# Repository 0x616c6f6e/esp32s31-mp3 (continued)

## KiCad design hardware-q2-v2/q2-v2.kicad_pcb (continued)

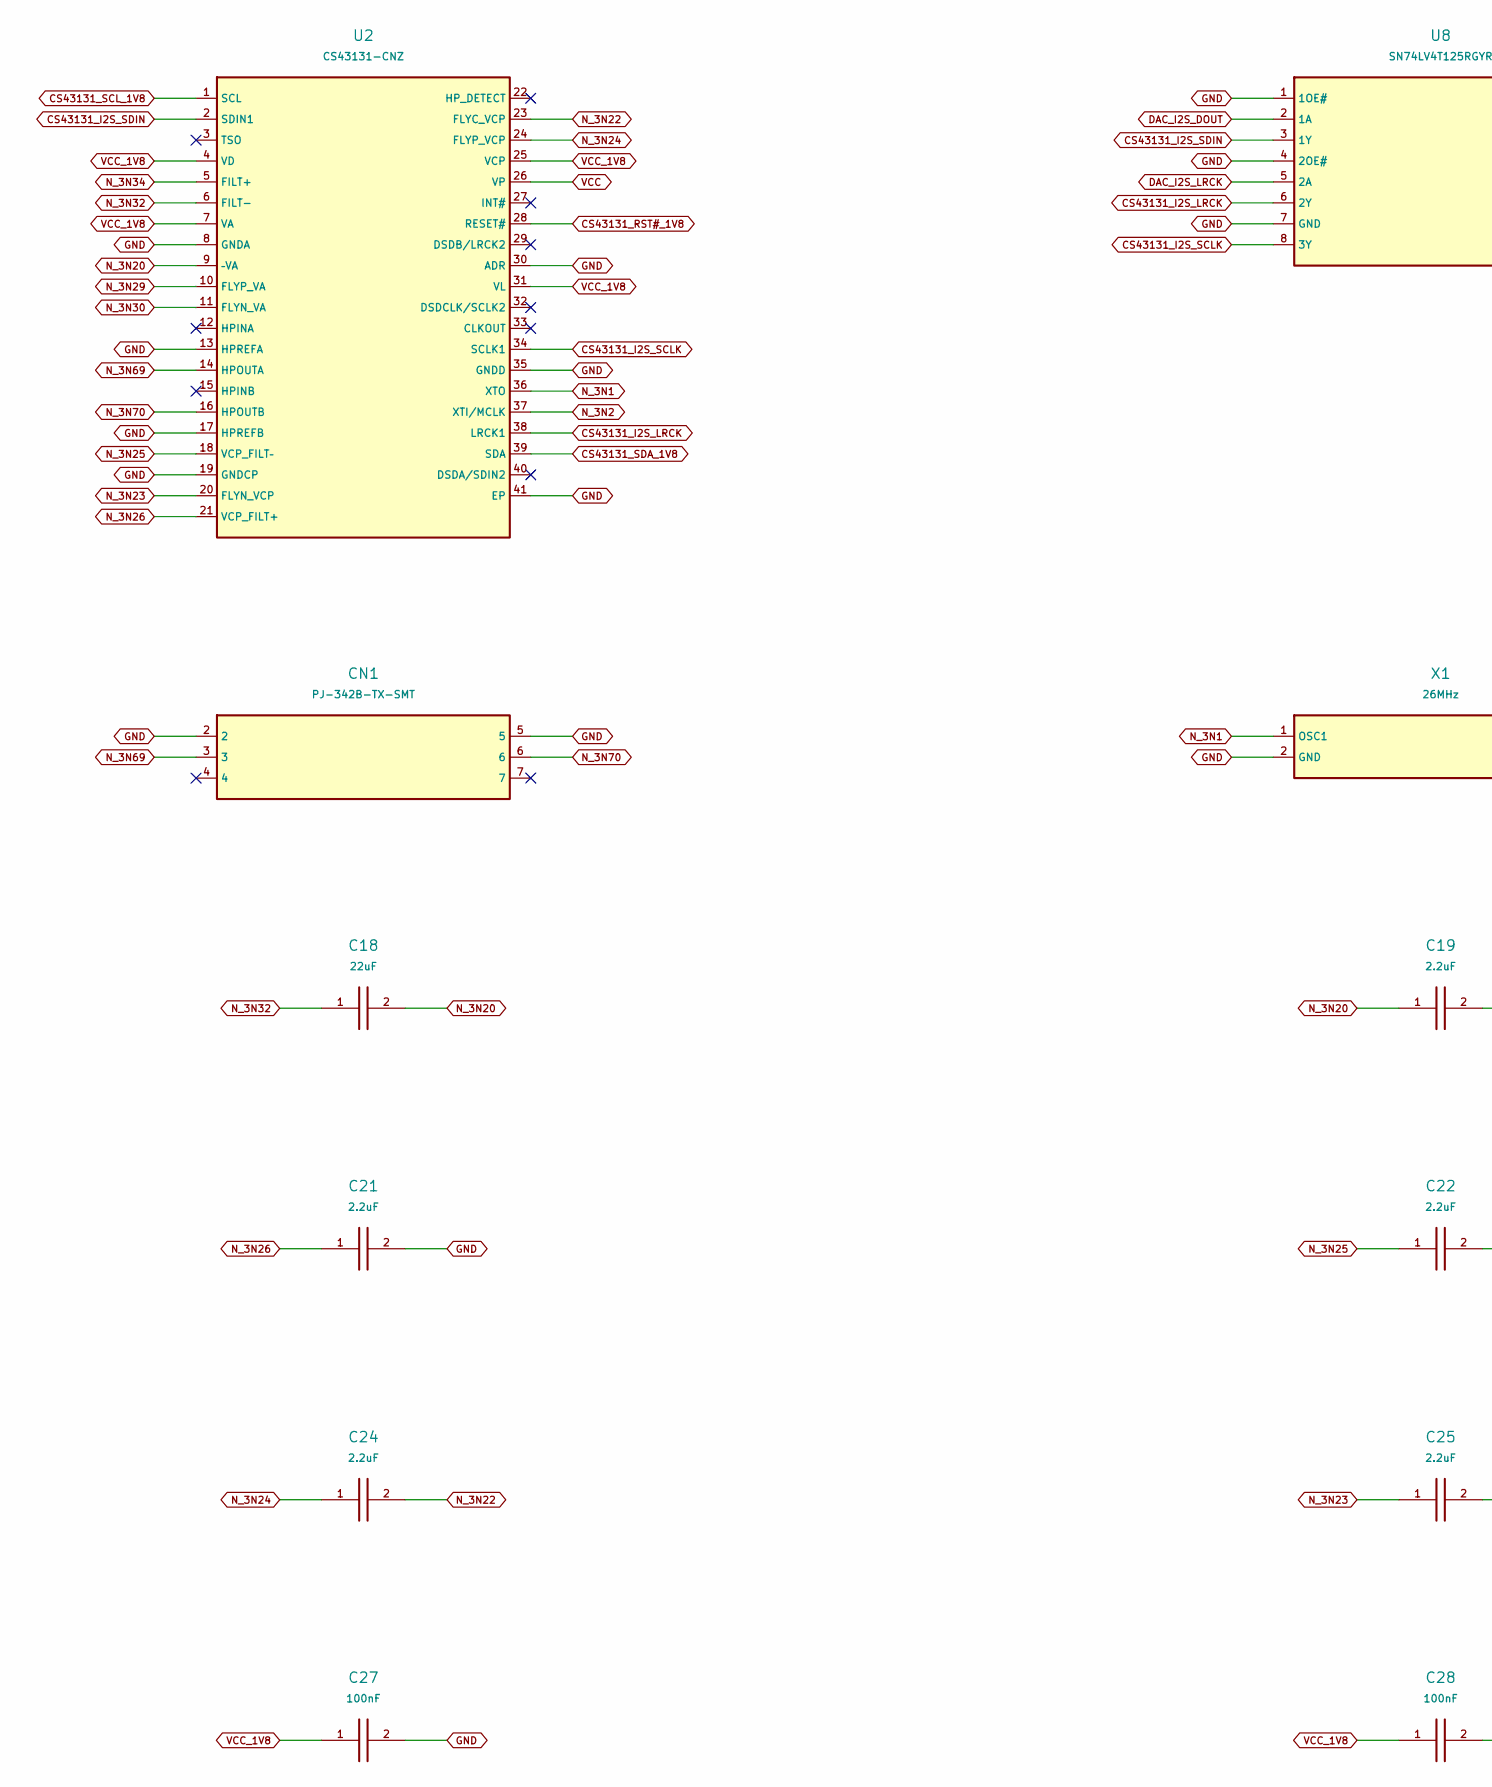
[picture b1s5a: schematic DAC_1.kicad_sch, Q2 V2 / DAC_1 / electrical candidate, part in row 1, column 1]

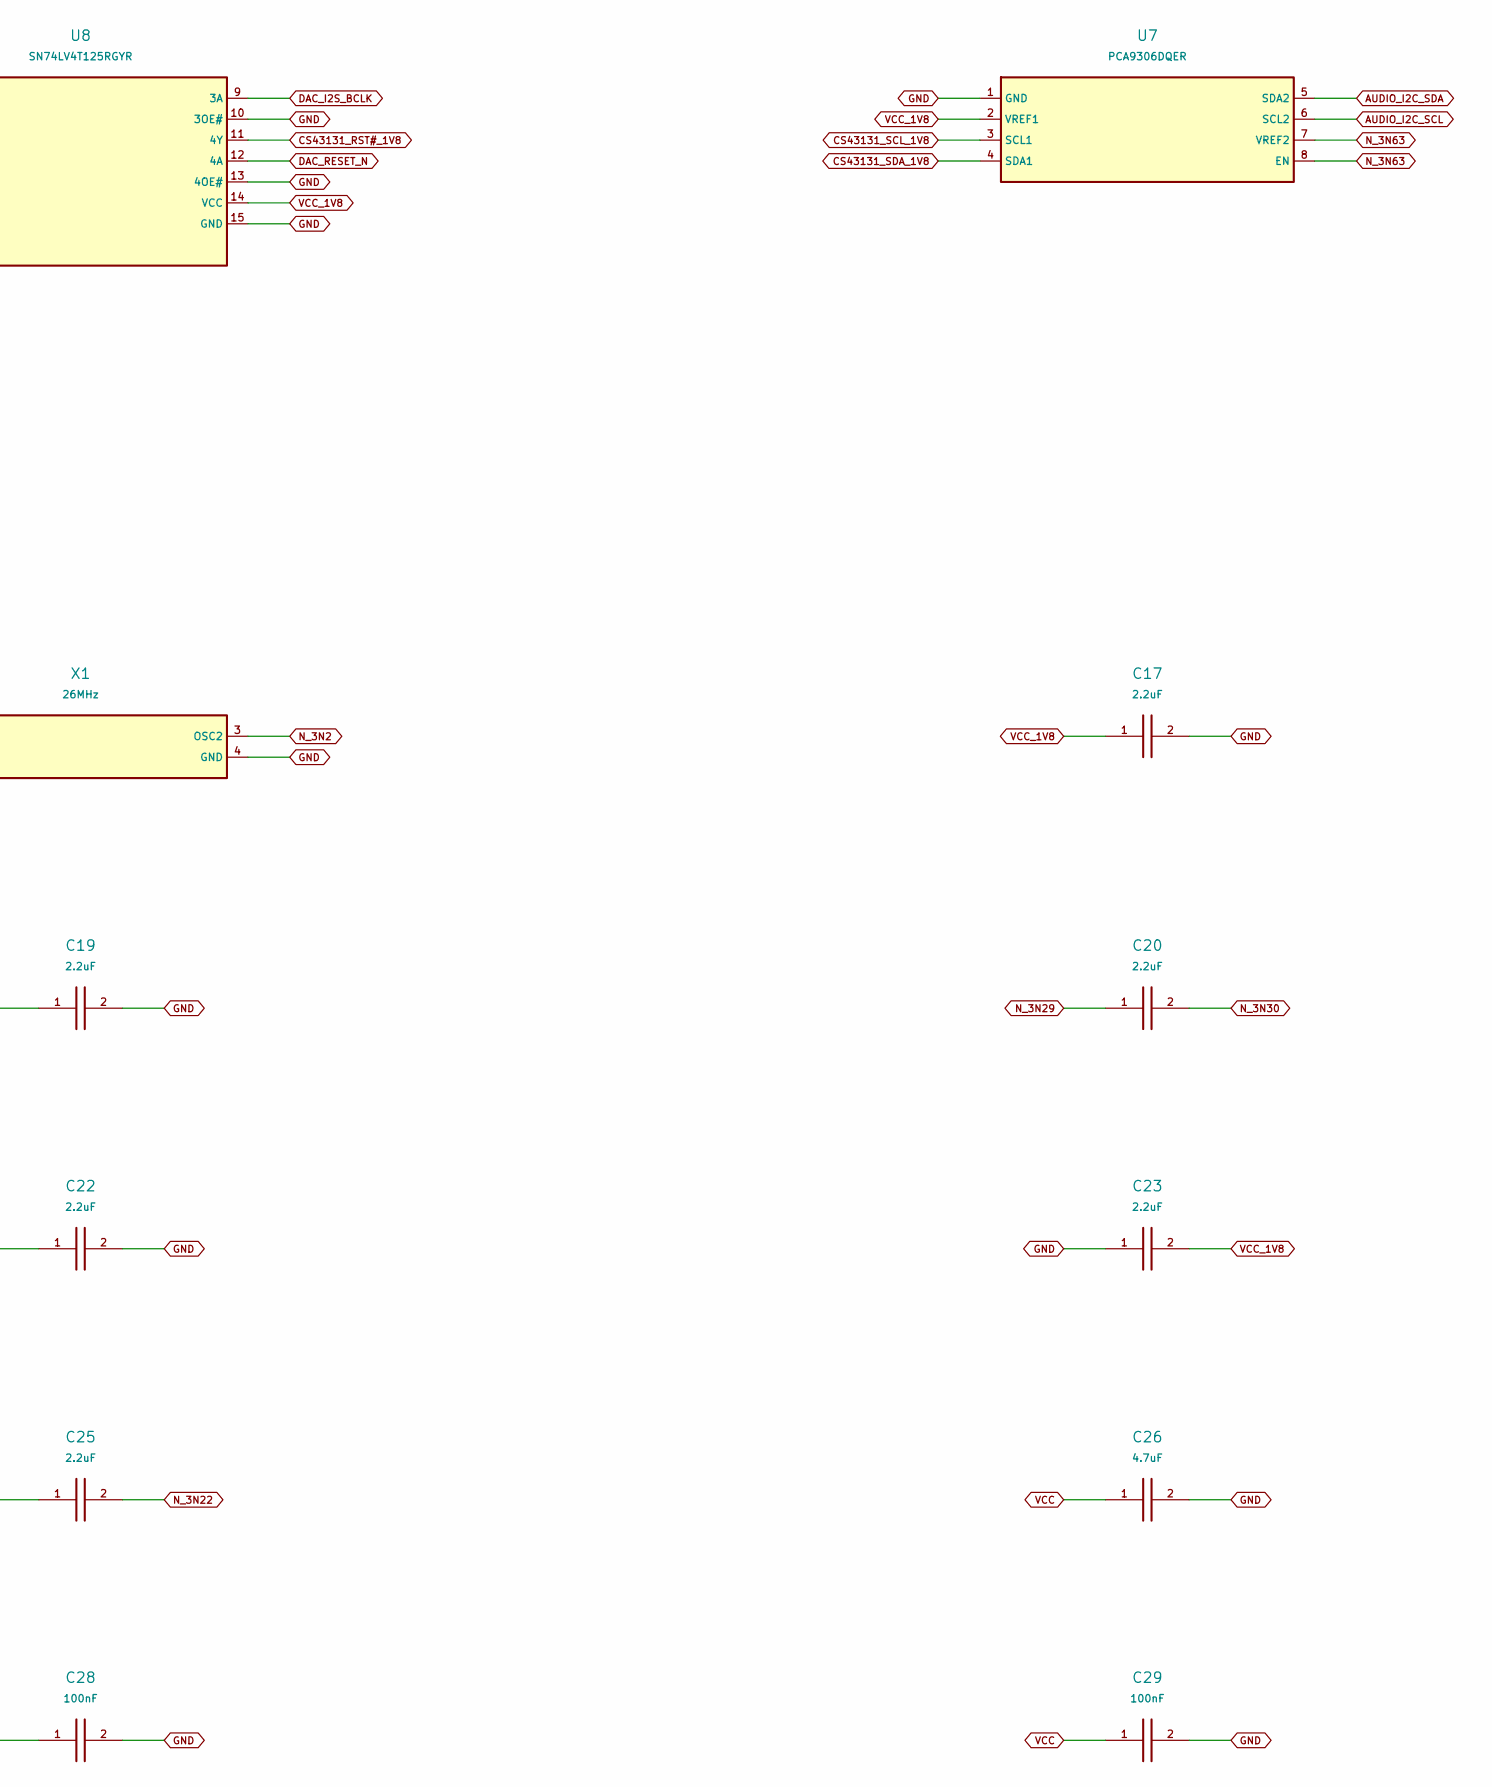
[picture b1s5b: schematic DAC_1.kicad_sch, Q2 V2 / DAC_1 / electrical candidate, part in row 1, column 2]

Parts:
C17, C19, C20, C21, C22, C23, C24, C25: 2.2uF; C_0402_1005Metric
C18: 22uF; FP_C18
C26: 4.7uF; C_0402_1005Metric
C27, C28, C29: 100nF; C_0402_1005Metric
CN1: PJ-342B-TX-SMT; FP_CN1
U2: CS43131-CNZ; FP_U2
U7: PCA9306DQER; FP_U7
U8: SN74LV4T125RGYR; FP_U8
X1: 26MHz; FP_X1

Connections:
AUDIO_I2C_SCL: U7.6 (SCL2); also elsewhere on the board
AUDIO_I2C_SDA: U7.5 (SDA2); also elsewhere on the board
CS43131_I2S_LRCK: U2.38 (LRCK1), U8.6 (2Y)
CS43131_I2S_SCLK: U2.34 (SCLK1), U8.8 (3Y)
CS43131_I2S_SDIN: U2.2 (SDIN1), U8.3 (1Y)
CS43131_RST#_1V8: U2.28 (RESET#), U8.11 (4Y)
CS43131_SCL_1V8: U2.1 (SCL), U7.3 (SCL1); also elsewhere on the board
CS43131_SDA_1V8: U2.39 (SDA), U7.4 (SDA1); also elsewhere on the board
DAC_I2S_BCLK: U8.9 (3A); also elsewhere on the board
DAC_I2S_DOUT: U8.2 (1A); also elsewhere on the board
DAC_I2S_LRCK: U8.5 (2A); also elsewhere on the board
DAC_RESET_N: U8.12 (4A); also elsewhere on the board
GND: C17.2, C19.2, C21.2, C22.2, C23.1, C26.2, C27.2, C28.2, C29.2, CN1.2, CN1.5, U2.8 (GNDA), U2.13 (HPREFA), U2.17 (HPREFB), U2.19 (GNDCP), U2.30 (ADR), U2.35 (GNDD), U2.41 (EP), U7.1 (GND), U8.1 (1OE#), U8.4 (2OE#), U8.7 (GND), U8.10 (3OE#), U8.13 (4OE#), U8.15 (GND), X1.2 (GND), X1.4 (GND); also elsewhere on the board
N_3N1: U2.36 (XTO), X1.1 (OSC1); also elsewhere on the board
N_3N2: U2.37 (XTI/MCLK), X1.3 (OSC2); also elsewhere on the board
N_3N20: C18.2, C19.1, U2.9 (–VA)
N_3N22: C24.2, C25.2, U2.23 (FLYC_VCP)
N_3N23: C25.1, U2.20 (FLYN_VCP)
N_3N24: C24.1, U2.24 (FLYP_VCP)
N_3N25: C22.1, U2.18 (VCP_FILT–)
N_3N26: C21.1, U2.21 (VCP_FILT+)
N_3N29: C20.1, U2.10 (FLYP_VA)
N_3N30: C20.2, U2.11 (FLYN_VA)
N_3N32: C18.1, U2.6 (FILT-)
N_3N34: U2.5 (FILT+); also elsewhere on the board
N_3N63: U7.7 (VREF2), U7.8 (EN); also elsewhere on the board
N_3N69: CN1.3, U2.14 (HPOUTA)
N_3N70: CN1.6, U2.16 (HPOUTB)
VCC: C26.1, C29.1, U2.26 (VP); also elsewhere on the board
VCC_1V8: C17.1, C23.2, C27.1, C28.1, U2.4 (VD), U2.7 (VA), U2.25 (VCP), U2.31 (VL), U7.2 (VREF1), U8.14 (VCC); also elsewhere on the board

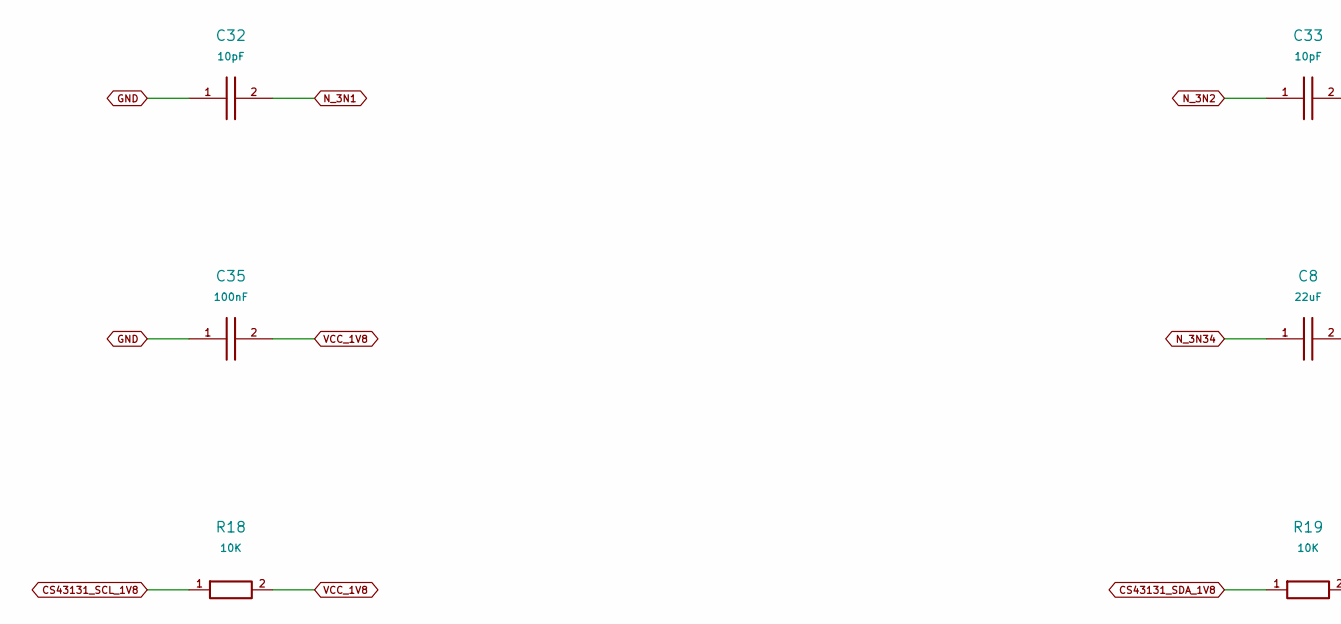
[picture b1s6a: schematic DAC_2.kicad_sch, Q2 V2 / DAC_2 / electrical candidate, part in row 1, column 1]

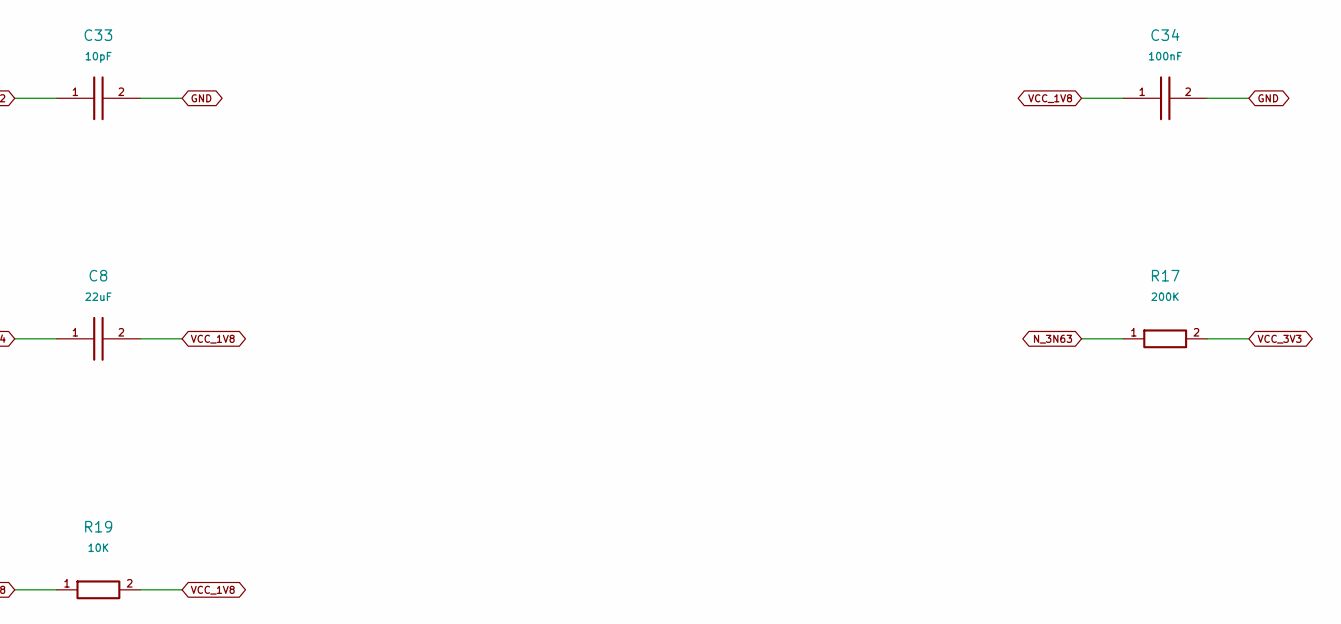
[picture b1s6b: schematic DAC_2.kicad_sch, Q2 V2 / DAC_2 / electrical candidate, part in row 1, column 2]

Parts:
C8: 22uF; FP_C8
C32, C33: 10pF; C_0402_1005Metric
C34, C35: 100nF; C_0402_1005Metric
R17: 200K; R_0402_1005Metric
R18, R19: 10K; R_0402_1005Metric

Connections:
CS43131_SCL_1V8: R18.1; also elsewhere on the board
CS43131_SDA_1V8: R19.1; also elsewhere on the board
GND: C32.1, C33.2, C34.2, C35.1; also elsewhere on the board
N_3N1: C32.2; also elsewhere on the board
N_3N2: C33.1; also elsewhere on the board
N_3N34: C8.1; also elsewhere on the board
N_3N63: R17.1; also elsewhere on the board
VCC_1V8: C8.2, C34.1, C35.2, R18.2, R19.2; also elsewhere on the board
VCC_3V3: R17.2; also elsewhere on the board

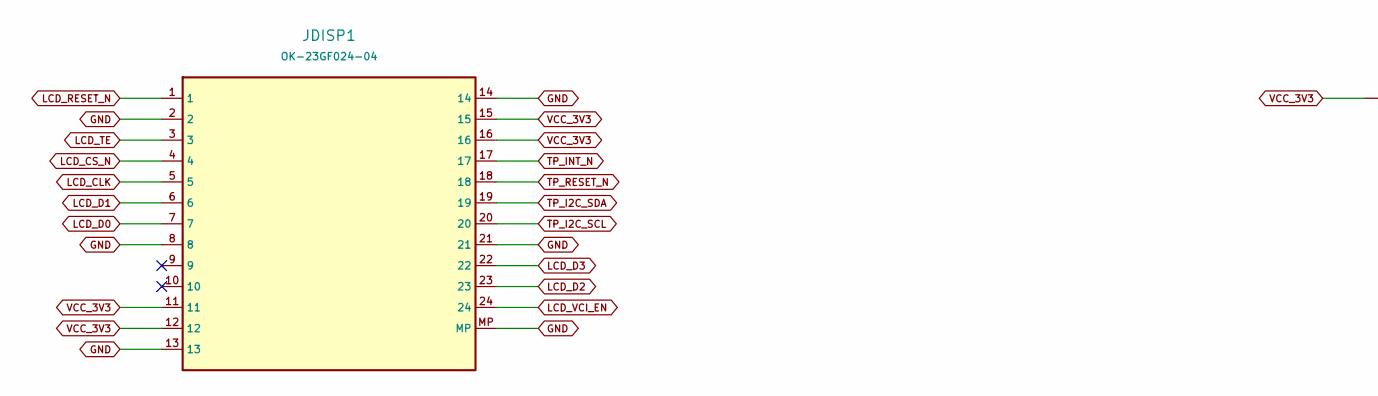
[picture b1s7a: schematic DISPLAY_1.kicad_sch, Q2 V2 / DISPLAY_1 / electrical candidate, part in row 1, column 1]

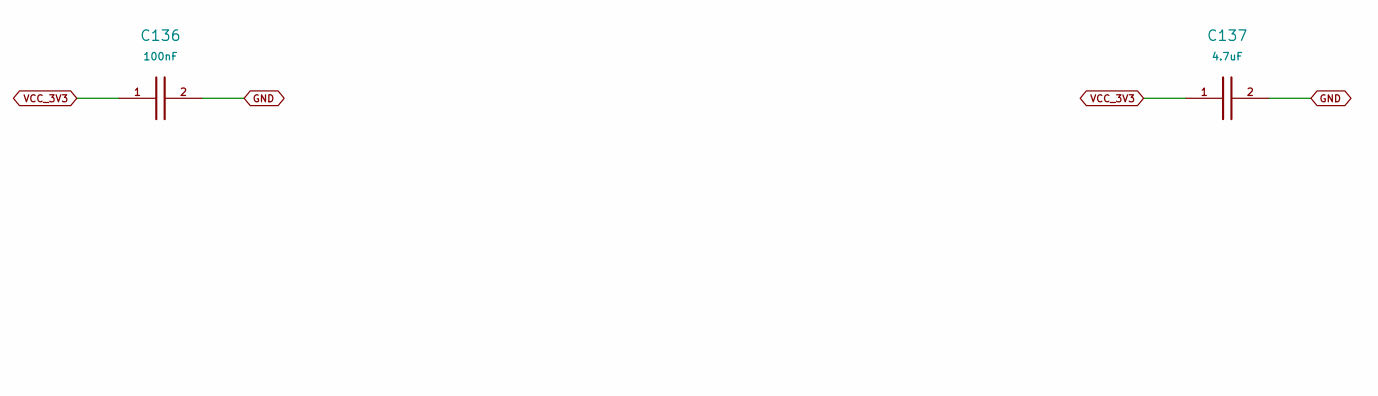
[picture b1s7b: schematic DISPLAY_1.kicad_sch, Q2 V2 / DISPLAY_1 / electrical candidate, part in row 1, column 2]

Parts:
C136: 100nF; C_0402_1005Metric
C137: 4.7uF; C_0402_1005Metric
JDISP1: OK-23GF024-04; FP_JDISP1

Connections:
GND: C136.2, C137.2, JDISP1.2, JDISP1.8, JDISP1.13, JDISP1.14, JDISP1.21, JDISP1.MP; also elsewhere on the board
LCD_CLK: JDISP1.5; also elsewhere on the board
LCD_CS_N: JDISP1.4; also elsewhere on the board
LCD_D0: JDISP1.7; also elsewhere on the board
LCD_D1: JDISP1.6; also elsewhere on the board
LCD_D2: JDISP1.23; also elsewhere on the board
LCD_D3: JDISP1.22; also elsewhere on the board
LCD_RESET_N: JDISP1.1; also elsewhere on the board
LCD_TE: JDISP1.3; also elsewhere on the board
LCD_VCI_EN: JDISP1.24; also elsewhere on the board
TP_I2C_SCL: JDISP1.20; also elsewhere on the board
TP_I2C_SDA: JDISP1.19; also elsewhere on the board
TP_INT_N: JDISP1.17; also elsewhere on the board
TP_RESET_N: JDISP1.18; also elsewhere on the board
VCC_3V3: C136.1, C137.1, JDISP1.11, JDISP1.12, JDISP1.15, JDISP1.16; also elsewhere on the board

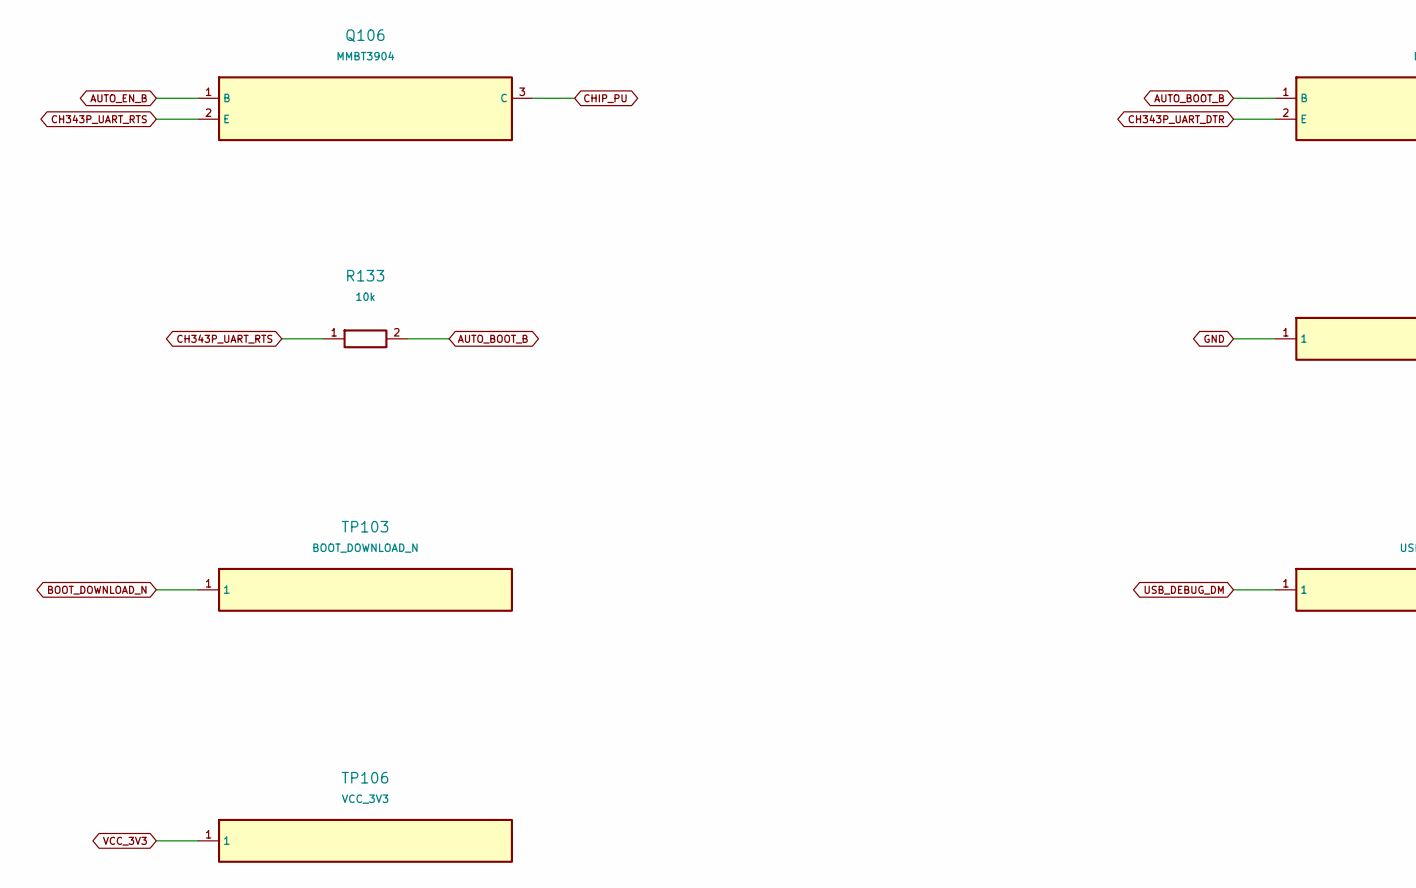
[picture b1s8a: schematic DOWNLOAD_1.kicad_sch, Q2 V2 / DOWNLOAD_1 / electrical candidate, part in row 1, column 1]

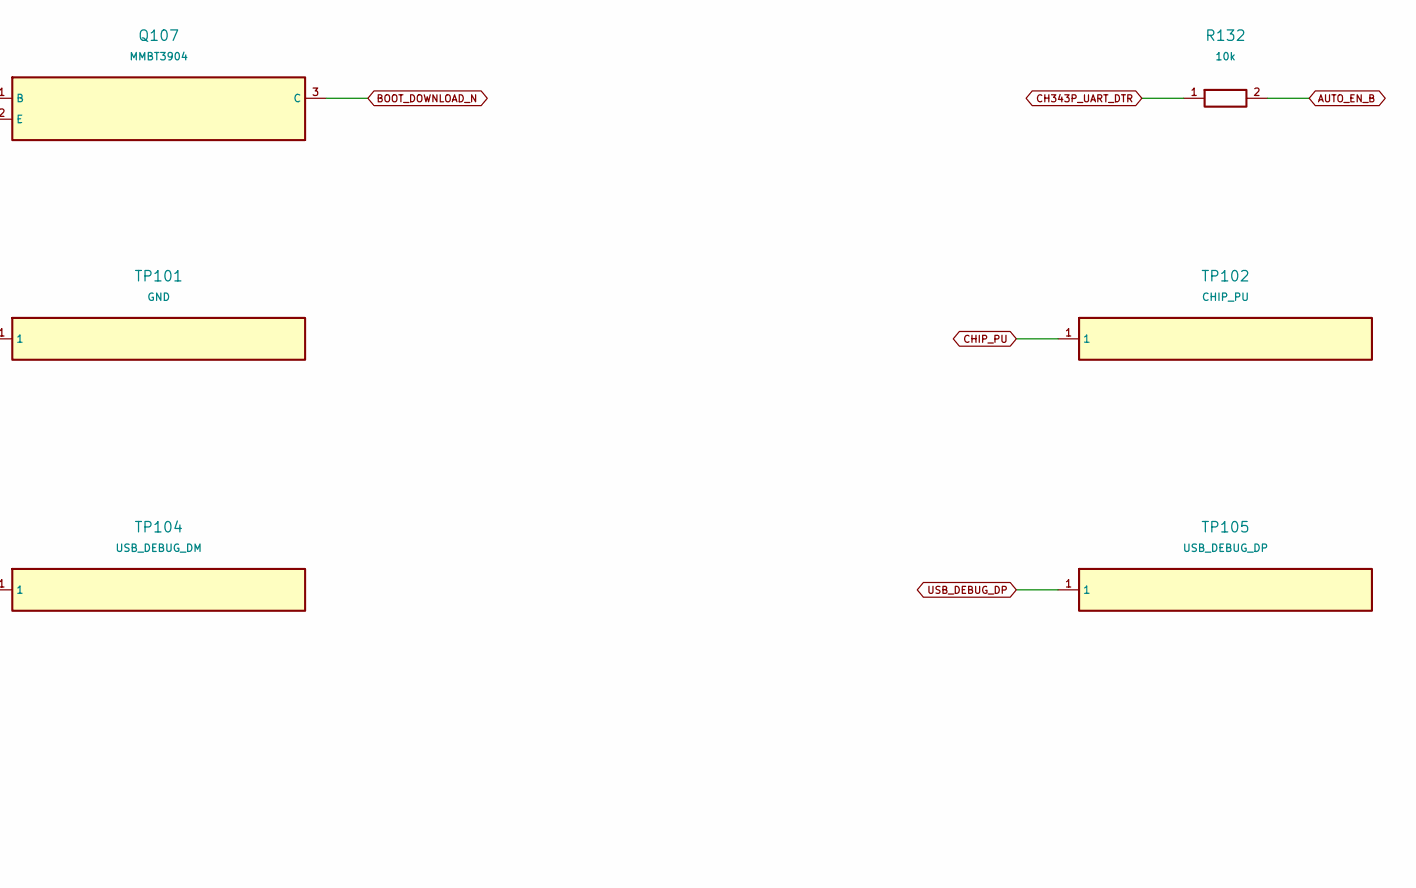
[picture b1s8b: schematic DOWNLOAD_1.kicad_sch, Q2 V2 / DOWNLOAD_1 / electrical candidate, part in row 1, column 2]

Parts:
Q106: MMBT3904; FP_Q106
Q107: MMBT3904; FP_Q107
R132, R133: 10k; R_0402_1005Metric
TP101: GND; FP_TP101
TP102: CHIP_PU; FP_TP102
TP103: BOOT_DOWNLOAD_N; FP_TP103
TP104: USB_DEBUG_DM; FP_TP104
TP105: USB_DEBUG_DP; FP_TP105
TP106: VCC_3V3; FP_TP106

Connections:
AUTO_BOOT_B: Q107.1 (B), R133.2
AUTO_EN_B: Q106.1 (B), R132.2
BOOT_DOWNLOAD_N: Q107.3 (C), TP103.1; also elsewhere on the board
CH343P_UART_DTR: Q107.2 (E), R132.1; also elsewhere on the board
CH343P_UART_RTS: Q106.2 (E), R133.1; also elsewhere on the board
CHIP_PU: Q106.3 (C), TP102.1; also elsewhere on the board
GND: TP101.1; also elsewhere on the board
USB_DEBUG_DM: TP104.1; also elsewhere on the board
USB_DEBUG_DP: TP105.1; also elsewhere on the board
VCC_3V3: TP106.1; also elsewhere on the board

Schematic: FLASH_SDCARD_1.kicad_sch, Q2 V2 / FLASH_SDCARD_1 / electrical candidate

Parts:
C49: 10uF; C_0402_1005Metric
C50: 100nF; C_0402_1005Metric
CARD2: TF PUSH; FP_CARD2

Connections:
GND: C49.1, C50.1, CARD2.6 (VSS), CARD2.10 (EP), CARD2.11 (EP), CARD2.12 (EP), CARD2.13 (EP); also elsewhere on the board
SD_CARD_DETECT_N: CARD2.CD; also elsewhere on the board
SD_CLK: CARD2.5 (CLX); also elsewhere on the board
SD_CMD: CARD2.3 (CMD); also elsewhere on the board
SD_D0: CARD2.7 (DAT0); also elsewhere on the board
SD_D1: CARD2.8 (DAT1); also elsewhere on the board
SD_D2: CARD2.1 (DAT2); also elsewhere on the board
SD_D3: CARD2.2 (CD/DAT3); also elsewhere on the board
VCC_3V3: C49.2, C50.2, CARD2.4 (VDD); also elsewhere on the board

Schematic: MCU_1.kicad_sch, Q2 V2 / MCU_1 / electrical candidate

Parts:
C13: 100nF; C_0402_1005Metric
C39: 1uF; C_0402_1005Metric
R6, R7, R10, R20, R22, R25, R26, R29, R30, R35, R36, R37, R38, R39, R42, R43, R44, R45, R46: 10K; R_0402_1005Metric

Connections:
AUDIO_I2C_SCL: R26.2; also elsewhere on the board
AUDIO_I2C_SDA: R30.2; also elsewhere on the board
BAT_ALERT_N: R6.2; also elsewhere on the board
BOOT_DOWNLOAD_N: R20.2; also elsewhere on the board
BOOT_MODE_H: R25.2; also elsewhere on the board
CHG_INT_N: R43.2; also elsewhere on the board
CHIP_PU: C39.1, R29.1; also elsewhere on the board
GND: C13.2, C39.2, R22.1, R44.1; also elsewhere on the board
MCU_VDD_SPI: C13.1; also elsewhere on the board
MOTOR_EN: R44.2; also elsewhere on the board
RTC_INT_N: R42.1; also elsewhere on the board
SD_CMD: R39.2; also elsewhere on the board
SD_D0: R38.2; also elsewhere on the board
SD_D1: R35.2; also elsewhere on the board
SD_D2: R36.2; also elsewhere on the board
SD_D3: R37.2; also elsewhere on the board
SYS_I2C_SCL: R7.2; also elsewhere on the board
TP_I2C_SCL: R45.2; also elsewhere on the board
TP_I2C_SDA: R46.2; also elsewhere on the board
USB_PATH_SEL: R10.2, R22.2; also elsewhere on the board
VCC_3V3: R6.1, R7.1, R10.1, R20.1, R25.1, R26.1, R29.2, R30.1, R35.1, R36.1, R37.1, R38.1, R39.1, R42.2, R43.1, R45.1, R46.1; also elsewhere on the board

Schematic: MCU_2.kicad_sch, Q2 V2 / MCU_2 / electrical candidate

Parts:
R8: 10K; R_0402_1005Metric

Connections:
SYS_I2C_SDA: R8.2; also elsewhere on the board
VCC_3V3: R8.1; also elsewhere on the board

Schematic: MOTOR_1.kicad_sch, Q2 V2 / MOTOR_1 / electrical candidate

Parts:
C4, C5: 1uF; C_0402_1005Metric
C58: 100nF; C_0402_1005Metric
CN3: Solder wire pads; FP_CN3
L3: BLM18KG601SN1D; FP_L3
U11: DRV2605LDGSR; FP_U11

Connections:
GND: C4.1, C5.1, C58.1, U11.4 (IN/TRIG), U11.8 (GND); also elsewhere on the board
MOTOR_EN: U11.5 (EN); also elsewhere on the board
MOTOR_OUT_N: CN3.2, U11.9 (OUT-)
MOTOR_OUT_P: CN3.1, U11.7 (OUT+)
N_5N6: C4.2, U11.1 (REG)
N_5N15: C5.2, C58.2, L3.1, U11.6 (VDD/NC), U11.10 (VDD)
SYS_I2C_SCL: U11.2 (SCL); also elsewhere on the board
SYS_I2C_SDA: U11.3 (SDA); also elsewhere on the board
VCC_PMID: L3.2; also elsewhere on the board

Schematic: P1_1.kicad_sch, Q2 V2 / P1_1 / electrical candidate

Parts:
SCREW1: FP_SCREW1
SCREW2: FP_SCREW2
SCREW3: FP_SCREW3
SCREW5: FP_SCREW5

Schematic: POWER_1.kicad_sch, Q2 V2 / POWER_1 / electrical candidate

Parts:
C1: 10uF; FP_C1
C2: 10uF; FP_C2
C3: 100nF; C_0402_1005Metric
C10: 10uF; FP_C10
C11: 47nF; C_0402_1005Metric
C12: 10uF; FP_C12
C14: 1uF; FP_C14
C15: 10uF; FP_C15
C16: 47uF; FP_C16
C30, C31: 1uF; C_0402_1005Metric
C43: 220nF; C_0402_1005Metric
CN2: Solder wire pads; FP_CN2
U3: DSCB_BQ25895RTW; FP_U3
U4: TLV62568DBVR; FP_U4
U5: ME6211C18M5G-N; FP_U5
U6: GEK100; FP_U6
U14: STC3115AIQT; FP_U14

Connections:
BAT_ALERT_N: U14.1 (ALM); also elsewhere on the board
BAT_TS: CN2.2, U3.11 (TS); also elsewhere on the board
BQ25895_CHG_EN#: U3.9 (~CE); also elsewhere on the board
CHG_INT_N: U3.7 (INT); also elsewhere on the board
CHG_OTG_EN: U3.8 (OTG); also elsewhere on the board
GBAT: CN2.3, U14.6 (CG); also elsewhere on the board
GEK_RST: U6.3 (RST); also elsewhere on the board
GND: C1.1, C2.1, C3.1, C10.1, C12.1, C14.1, C15.1, C16.2, C30.1, C31.1, C43.2, U3.17 (PGND), U3.18 (PGND), U3.25 (PGND), U4.2 (GND), U5.2 (VSS), U6.2 (GND), U14.5 (GND); also elsewhere on the board
KEY_RAW_N: U6.1 (KEY); also elsewhere on the board
N_2N13: C11.1, U3.21 (BTST)
N_2N14: C11.2, U3.19 (SW), U3.20 (SW); also elsewhere on the board
N_2N16: U3.22 (REGN); also elsewhere on the board
N_2N19: U3.10 (ILIM); also elsewhere on the board
N_2N84: U4.3 (SW); also elsewhere on the board
N_2N86: U4.5 (FB); also elsewhere on the board
N_2N133: U14.8 (BATD/CD); also elsewhere on the board
N_2N157: U14.10 (VIN); also elsewhere on the board
PWR_3V3_EN: U4.1 (EN), U6.5 (OUTH); also elsewhere on the board
SYS_I2C_SCL: U3.5 (SCL), U14.3 (SCL); also elsewhere on the board
SYS_I2C_SDA: U3.6 (SDA), U14.2 (SDA); also elsewhere on the board
VBAT: C10.2, C43.1, CN2.1, U3.13 (BAT), U3.14 (BAT), U14.9 (VCC); also elsewhere on the board
VBUS_5V: C14.2, U3.1 (VBUS); also elsewhere on the board
VCC: C1.2, C3.2, C12.2, C15.2, C30.2, U3.15 (SYS), U3.16 (SYS), U4.4 (VIN), U5.1 (VIN), U5.3 (CE); also elsewhere on the board
VCC_1V8: C31.2, U5.5 (VOUT); also elsewhere on the board
VCC_3V3: C2.2; also elsewhere on the board
VCC_3V3_AON: U6.6 (VDD); also elsewhere on the board
VCC_PMID: C16.1, U3.23 (PMID); also elsewhere on the board

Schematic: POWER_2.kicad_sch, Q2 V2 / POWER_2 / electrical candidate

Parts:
C9: 4.7uF; FP_C9
C61: 220nF; C_0402_1005Metric
D2: B5817W; FP_D2
L1: 2.2uH; FP_L1
L2: 2.2uH; FP_L2
R1: 10mΩ; FP_R1
R2, R33: 1K; R_0402_1005Metric
R3: 22K1; R_0402_1005Metric
R4, R5, R11, R12: 100K; R_0402_1005Metric
R9: 700R; R_0402_1005Metric
R13: 5K23; R_0402_1005Metric
R14: 30K1; R_0402_1005Metric
R34: 0R; R_0402_1005Metric

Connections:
BAT_TS: R13.2, R14.2; also elsewhere on the board
BQ25895_CHG_EN#: R11.2; also elsewhere on the board
CHG_OTG_EN: R12.2; also elsewhere on the board
GBAT: R1.1, R34.1; also elsewhere on the board
GND: C9.2, C61.2, R1.2, R3.1, R5.1, R9.1, R11.1, R12.1, R14.1; also elsewhere on the board
N_2N14: D2.2 (A), L2.1; also elsewhere on the board
N_2N16: C9.1, R13.1; also elsewhere on the board
N_2N19: R9.2; also elsewhere on the board
N_2N84: L1.1; also elsewhere on the board
N_2N86: R3.2, R4.1; also elsewhere on the board
N_2N133: R33.1; also elsewhere on the board
N_2N135: R33.2, R34.2
N_2N157: C61.1, R2.1; also elsewhere on the board
PWR_3V3_EN: R5.2; also elsewhere on the board
VBAT: R2.2; also elsewhere on the board
VCC: L2.2; also elsewhere on the board
VCC_3V3: L1.2, R4.2; also elsewhere on the board
VCC_PMID: D2.1 (C); also elsewhere on the board

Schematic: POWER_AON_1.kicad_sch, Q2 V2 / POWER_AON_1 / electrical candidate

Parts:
C130, C131: 2.2uF; C_0402_1005Metric
C132, C134, C135: 100nF; C_0402_1005Metric
C133: 1uF; C_0402_1005Metric
Q101: BSS138; FP_Q101
Q102: BSS138; FP_Q102
Q103: BSS138; FP_Q103
Q104: BSS138; FP_Q104
Q105: BSS138; FP_Q105
R128: 10k; R_0402_1005Metric
R129, R131: 100k; R_0402_1005Metric
R130: 200k; R_0402_1005Metric
U20: TLV75533PDBVR; FP_U20
U21: SN74LVC1G123DCUR; FP_U21

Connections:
CTRL_INT_AON_N: Q103.3 (D); also elsewhere on the board
CTRL_INT_N: Q103.2 (S); also elsewhere on the board
CTRL_RESET_AON_N: Q104.3 (D); also elsewhere on the board
CTRL_RESET_N: Q104.2 (S), R128.2; also elsewhere on the board
CTRL_SCL_AON: Q102.3 (D); also elsewhere on the board
CTRL_SDA_AON: Q101.3 (D); also elsewhere on the board
GEK_RST: U21.5 (Q); also elsewhere on the board
GND: C130.2, C131.2, C132.2, C134.2, C135.2, R129.2, U20.2 (GND), U21.1 (A_N), U21.4 (GND); also elsewhere on the board
KEY_POWER_SENSE_N: Q105.2 (S); also elsewhere on the board
KEY_RAW_N: Q105.3 (D); also elsewhere on the board
OFF_CEXT: C133.1, U21.6 (CEXT)
OFF_CLEAR_N: C134.1, R131.2, U21.3 (CLR_N)
OFF_RC: C133.2, R130.2, U21.7 (REXT_CEXT)
POWER_OFF_REQ: R129.1, U21.2 (B); also elsewhere on the board
SYS_I2C_SCL: Q102.2 (S); also elsewhere on the board
SYS_I2C_SDA: Q101.2 (S); also elsewhere on the board
VCC: C130.1, U20.1 (IN), U20.3 (EN); also elsewhere on the board
VCC_3V3: Q101.1 (G), Q102.1 (G), Q103.1 (G), Q104.1 (G), Q105.1 (G), R128.1; also elsewhere on the board
VCC_3V3_AON: C131.1, C132.1, C135.1, R130.1, R131.1, U20.5 (OUT), U21.8 (VCC); also elsewhere on the board

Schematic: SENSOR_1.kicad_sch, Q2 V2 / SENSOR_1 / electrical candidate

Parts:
C6, C7, C47, C48, C53: 100nF; C_0402_1005Metric
C54: 1uF; C_0402_1005Metric
U1: RX8130CE:BB; FP_U1
U15: LSM6DS3TR-C; FP_U15

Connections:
AUDIO_I2C_SCL: U15.13 (SCL); also elsewhere on the board
AUDIO_I2C_SDA: U15.14 (SDA); also elsewhere on the board
GND: C6.2, C7.2, C47.2, C48.2, C53.2, C54.2, U1.7 (GND), U15.2 (SDx), U15.3 (SCx), U15.6 (GND), U15.7 (GND); also elsewhere on the board
IMU_INT1: U15.4 (INT1); also elsewhere on the board
N_7N55: C54.1, U1.9 (VOUT)
RTC_INT_N: U1.6 (#IRQ); also elsewhere on the board
SYS_I2C_SCL: U1.2 (SCL); also elsewhere on the board
SYS_I2C_SDA: U1.3 (SDA); also elsewhere on the board
VBAT: C7.1, U1.10 (VBAT); also elsewhere on the board
VCC_3V3: C6.1, C47.1, C48.1, C53.1, U1.1 (Vio), U1.8 (VDD), U15.1 (SDO/SA0), U15.5 (VDDIO), U15.8 (VDD), U15.12 (CS); also elsewhere on the board

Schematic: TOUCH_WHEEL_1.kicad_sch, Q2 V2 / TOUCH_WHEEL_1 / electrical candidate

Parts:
C59: 100nF; C_0402_1005Metric
FPC1: HC-FPC-05-10-12RLTAG; FP_FPC1

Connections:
CTRL_INT_AON_N: FPC1.5; also elsewhere on the board
CTRL_RESET_AON_N: FPC1.6; also elsewhere on the board
CTRL_SCL_AON: FPC1.4; also elsewhere on the board
CTRL_SDA_AON: FPC1.3; also elsewhere on the board
GND: C59.2, FPC1.1, FPC1.12, FPC1.13, FPC1.14; also elsewhere on the board
KEY_RAW_N: FPC1.11; also elsewhere on the board
VCC_3V3: C59.1; also elsewhere on the board
VCC_3V3_AON: FPC1.2; also elsewhere on the board

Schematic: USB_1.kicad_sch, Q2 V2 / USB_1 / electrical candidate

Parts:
C36, C37, C38, C44, C51: 100nF; C_0402_1005Metric
D1: USBLC6-2SC6; FP_D1
R21: 100K; R_0402_1005Metric
R31, R32: 5K1; R_0402_1005Metric
U12: CH343P; FP_U12
U17: SGM7229YMS10G/TR; FP_U17
USB1: TYPE-C 16PIN 2MD(073); FP_USB1

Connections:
CH343P_UART_DTR: U12.12 (DTRTNOW); also elsewhere on the board
CH343P_UART_RTS: U12.13 (RTS); also elsewhere on the board
CH343P_USB_DN: U12.8 (UD-), U17.8 (HSD2-)
CH343P_USB_DP: U12.7 (UD+), U17.9 (HSD2+)
GND: C36.2, C37.2, C38.2, C44.2, C51.2, D1.2 (GND), R21.1, R31.1, R32.1, U12.2 (GND), U12.17 (EP), U17.5 (GND), USB1.13 (EH), USB1.14 (EH), USB1.A1B12 (GND), USB1.B1A12 (GND); also elsewhere on the board
N_6N45: R32.2, USB1.B5 (CC2)
N_6N46: R31.2, USB1.A5 (CC1)
N_6N67: C38.1, U12.6 (V3)
SGM7227_EN#: R21.2, U17.10 (OE#)
TYPEC_USB_DN: D1.4 (I/O2), U17.4 (D-)
TYPEC_USB_DN_IN: D1.3 (I/O2), USB1.A7 (Dn1), USB1.B7 (Dn2)
TYPEC_USB_DP: D1.6 (I/O1), U17.3 (D+)
TYPEC_USB_DP_IN: D1.1 (I/O1), USB1.A6 (Dp1), USB1.B6 (Dp2)
UART0_RX: U12.4 (TXD); also elsewhere on the board
UART0_TX: U12.5 (RXD); also elsewhere on the board
USB_HS_DM: U17.6 (HSD1-); also elsewhere on the board
USB_HS_DP: U17.7 (HSD1+); also elsewhere on the board
USB_PATH_SEL: U17.2 (S); also elsewhere on the board
VBUS_5V: C36.1, C44.1, C51.1, D1.5 (VBUS), U12.3 (VDD5), U12.9 (VBUS), U17.1 (VCC), USB1.A4B9 (VBUS), USB1.B4A9 (VBUS); also elsewhere on the board
VCC_3V3: C37.1, U12.1 (VIO); also elsewhere on the board
